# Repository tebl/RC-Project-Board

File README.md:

# RC Project Board
This year I went as far as getting myself one of those electronic games advent calendards, the kind where you get a book, a handful of components and then you get to build some a few different games using those components. Unfortunately it's one of those that only comes with a pre-programmed microcontroller and no sourcecode, so it never felt like I was building much of anything - just randomly inserting components into undocumented pins and then hope that the anonymous black box does most of the fun stuff!

Never got to the end of the book, if I'm going to build it then I'm going to build it using either an Arduino or one of my retro-computer builds - so, this project was created as a way of probably someday doing all of those things. This project is composed of two separate parts, the projet platforms boards that the retro-computer builds plugs into and the various projects that you either construct yourself on a breadboard or slot on top one of the provided PCB designs.

Pictured above is how my [RC-ONE](https://github.com/tebl/RC-ONE) looks while slotted into the [6502 Project Platform](https://github.com/tebl/RC-Project-Board/tree/master/platforms/PP%206502), the [PB-002 Covox Sound](https://github.com/tebl/RC-Project-Board/tree/master/projects/PB-002%20Covox%20Sound) project has been slotted on top instead of the usual breadboard. Below that is the [6502 Project Platform](https://github.com/tebl/RC-Project-Board/tree/master/platforms/PP%206502) with a 400 point breadboard fitting neatly on the board, if you want more space to play around you could also use the 830 point breadboard with parts of it hanging over the sides - not pretty, but oh so practical!

## Project platforms
To keep things somewhat on the simple side of things I've decided to limit myself to just doing digital I/O, leaving all of the analog stuff at the door - probably a project for another rainy day! Therefore in the context of this project I'm defining a project platform as any system capable of providing at least 16 digital I/O lines, each consists of a dedicated PCB that should take care of connecting the things together in the fashion expected by each project. Sound difficult? That just means you're probably overthinking things, the general idea is to make it so that each project would look and connects the same way no matter the platform used.

The following project platforms have been made available, refer to the table below for an overview of platforms including a separate listing each of my retro-computers that can be used with that specific platform. Note that while I hope people'll build all of my designs, you'll only need a single platform board and one of the associated systems to connect to it to get started.

| Platform | Supported system |
| -------- | --------- |
| [6502](https://github.com/tebl/RC-Project-Board/tree/master/platforms/PP%206502) | [BE6502: Build a 6502 computer](https://github.com/tebl/BE6502) |
|  | [RC-ONE: KIM-1 Replica](https://github.com/tebl/RC-ONE) |
|  | [RC6502: Apple 1 Replica](https://github.com/tebl/RC6502-Apple-1-Replica) |
|  | [RC6802 Microchicken](https://github.com/tebl/RC6802-Microchicken) |
| [Arduino](https://github.com/tebl/RC-Project-Board/tree/master/platforms/PP%20Arduino) | Arduino Nano |

## Projects
The projects are whatever you'd like to build for yourself, but if you're just looking for ideas on a few fun projects to play around with then I've probably got you covered as long as you're not looking for the most advanced stuff from someone who just dabbles in simple electronics. Most of the projects can be constructed on the breadboard by themselves by connecting the signals using female to male dupont wires (*seems most reliable that way*), but a few of the more advanced one will also come with their own PCB-designs that you can opt to build instead - these just slot on top of the platform board instead.

The breadboard oriented designs will be prefixed **BB** and a project number, similarly the ones with their own PCBs have been prefixed **PB** instead. The project number probably won't carry all that much meaning over time, so just pick something that sounds interesting and have a go at building it! Given the differences in platforms the code'll be somewhat or even completely different for each of the various systems, so there'll be varying amounts of code available for each - on the other hand, converting between them or coming up with your own versions of the code will probably be where most of the fun is at.

| Project | Description |
| ------- | ----------- |
| [PB-001 Prototyping](https://github.com/tebl/RC-Project-Board/tree/master/projects/PB-001%20Prototyping) * | Used when moving design from breadboard to a soldered together version |
| [PB-002 Covox Sound](https://github.com/tebl/RC-Project-Board/tree/master/projects/PB-002%20Covox%20Sound) * | Build a Covox sound card (sort of) |
| [PB-003 LED Cube](https://github.com/tebl/RC-Project-Board/tree/master/projects/PB-003%20LED%20Cube) * | Build one of those fancy 4x4 LED cubes |

*) Project has not been completely tested

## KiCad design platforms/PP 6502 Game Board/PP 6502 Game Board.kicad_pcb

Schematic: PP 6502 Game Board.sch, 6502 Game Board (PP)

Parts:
C1, C2, C3, C4, C5, C6, C7, C8: 100nF; C_Disc_D4.7mm_W2.5mm_P5.00mm
J1: BASE; Pin_Header_Straight_2x06_Pitch2.54mm
J2: BTM; Pin_Header_Straight_1x39_Pitch2.54mm
J3: TOP; Pin_Header_Straight_1x39_Pitch2.54mm
J4: SBC; Pin_Header_Straight_1x39_Pitch2.54mm
J5: TRS_3.5mm; Tayda_3.5mm_stereo_TRS_jack_A-853
JP1: SPKR_EN; Pin_Header_Straight_1x02_Pitch2.54mm
JP3: VIA_CLK; Pin_Header_Straight_1x03_Pitch2.54mm
LS1: Speaker; Mini_Speaker
M1, M2, M3, M4: Mounting; 1pin
Q1: 2N2222; TO-92_Molded_Narrow
R1: 100; R_Axial_DIN0207_L6.3mm_D2.5mm_P10.16mm_Horizontal
R16: 3k3; R_Axial_DIN0207_L6.3mm_D2.5mm_P10.16mm_Horizontal
R17: 470; R_Axial_DIN0207_L6.3mm_D2.5mm_P10.16mm_Horizontal
R18: 1k; R_Axial_DIN0207_L6.3mm_D2.5mm_P10.16mm_Horizontal
U1, U3: 74LS138; DIP-16_W7.62mm_Socket_LongPads
U2: 6522 VIA1; DIP-40_W15.24mm_Socket_LongPads
U4, U5, U6: 7416; DIP-14_W7.62mm_Socket
U7: 6522 VIA3; DIP-40_W15.24mm_Socket_LongPads
U8: 74LS154; DIP-24_W15.24mm_LongPads

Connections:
/4K2: J1.1, U1.14 (O1)
/4K4: J1.3, U1.13 (O2)
/4K6: J1.5, U1.12 (O3)
/4K8: J1.7, U1.11 (O4)
/4KA: J1.9, U1.10 (O5)
/4KC: J1.11, U1.9 (O6)
/A0: J4.16, U2.38, U7.38
/A1: J4.15, U2.37, U7.37
/A2: J4.14, U2.36, U7.36
/A3: J4.13, U2.35, U7.35
/A9: J4.7, U3.1 (A0)
/A10: J4.6, U3.2 (A1)
/A11: J4.5, U3.3 (A2)
/A12: J4.4, U1.5 (E2)
/A13: J4.3, U1.1 (A0)
/A14: J4.2, U1.2 (A1)
/A15: J4.1, U1.3 (A2)
/D0: J4.27, U2.33, U7.33
/D1: J4.28, U2.32, U7.32
/D2: J4.29, U2.31, U7.31
/D3: J4.30, U2.30, U7.30
/D4: J4.31, U2.29, U7.29
/D5: J4.32, U2.28, U7.28
/D6: J4.33, U2.27, U7.27
/D7: J4.34, U2.26, U7.26
/KEY_0: J3.26, U8.1 (S0)
/KEY_1: J3.25, U8.2 (S1)
/KEY_2: J3.24, U8.3 (S2)
/KEY_3: J3.23, U8.4 (S3)
/KEY_4: J3.22, U8.5 (S4)
/KEY_5: J3.21, U8.6 (S5)
/KEY_6: J3.20, U8.7 (S6)
/KEY_7: J3.19, U8.8 (S7)
/KEY_8: J3.18, U8.9 (S8)
/KEY_9: J3.17, U8.10 (S9)
/KEY_A: J3.16, U8.11 (S10)
/KEY_B: J3.11, U8.13 (S11)
/KEY_C: J3.12, U8.14 (S12)
/KEY_D: J3.13, U8.15 (S13)
/KEY_E: J3.14, U8.16 (S14)
/KEY_F: J3.15, U8.17 (S15)
/KEY_R: J3.8, R16.2, U7.9
/LED1: J3.38, U4.2
/LED2: J3.37, U4.4
/LED3: J3.36, U4.6
/LED4: J3.35, U4.8
/LED5: J3.34, U4.10
/LED6: J3.33, U4.12
/LED7: J3.32, U5.2
/LED8: J3.31, U5.4
/LED9: J3.30, U5.6
/LED10: J2.33, U5.8
/LED11: J2.34, U5.10
/LED12: J2.35, U5.12
/LED13: J2.38, U6.2
/LED14: J2.37, U6.4
/LED15: J2.36, U6.6
/PHI0: J4.21, JP3.3
/PHI2: J4.19, JP3.1
/R/~W: J4.24, U2.22, U7.22
/~IRQ: J4.22, U2.21
/~RST: J4.20, U2.34, U7.34
CLOCK: JP3.2, U2.25, U7.25
unnamed: J1.2, J1.4, J1.6, J1.8, J1.10, J1.12, U3.5 (E2)
unnamed: J5.2, J5.5, R1.2
unnamed: JP1.1, Q1.2, R18.2
unnamed: JP1.2, R1.1, U7.17
unnamed: LS1.1, Q1.3, R17.1
unnamed: U2.2, U4.1
unnamed: U2.3, U4.3
unnamed: U2.4, U4.5
unnamed: U2.5, U4.9
unnamed: U2.6, U4.11
unnamed: U2.7, U4.13
unnamed: U2.8, U5.1
unnamed: U2.9, U5.3
unnamed: U2.10, U5.5
unnamed: U2.11, U5.9
unnamed: U2.12, U5.11
unnamed: U2.13, U5.13
unnamed: U2.14, U6.1
unnamed: U2.15, U6.3
unnamed: U2.17, U6.5
unnamed: U7.10, U8.23 (A0)
unnamed: U7.11, U8.22 (A1)
unnamed: U7.12, U8.21 (A2)
unnamed: U7.13, U8.20 (A3)
VCC: C1.1, C2.1, C3.1, C4.1, C5.1, C6.1, C7.1, C8.1, J2.1, J2.39, J3.1, J3.39, J4.18, R16.1, R17.2, R18.1, U1.6 (E3), U1.16 (VCC), U2.20, U2.24, U3.6 (E3), U3.16 (VCC), U4.14, U5.14, U6.14, U7.20, U7.24, U8.24 (VCC)
~VIA1: U2.23, U3.15 (O0)
~VIA3: U3.9 (O6), U7.23

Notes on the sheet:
$2000
$4000
$6000
$8000
$A000
$C000
$x000
$xE00
$x400
$x200
$x600
$x800
$xC00
$xA00
Rodney Zaks wrote a whole book of games for the SYM-1 and I wanted to build it for use with my computers as well. so this board takes care of the logic needed for a 6502 or 6800 based computer. Also requires the game board project fitted on top as it contains all of the interactive parts needed.

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
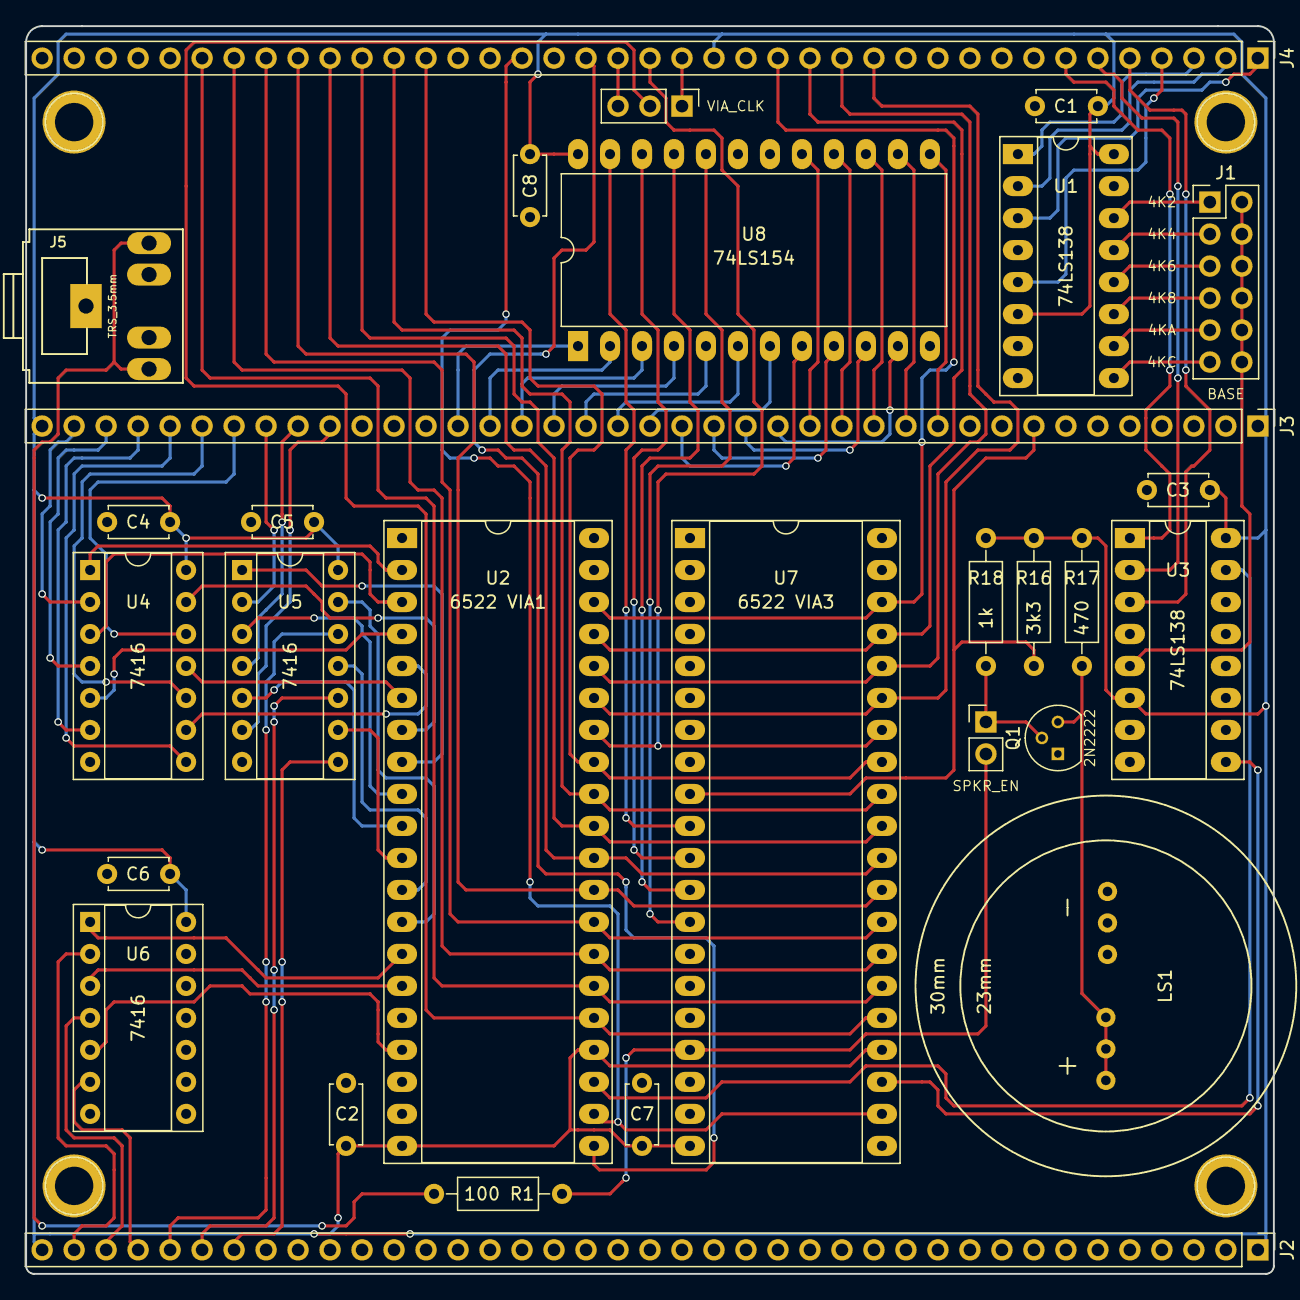
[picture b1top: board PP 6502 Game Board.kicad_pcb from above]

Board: 2 copper layers, 99.1 x 99.1 mm, 33 parts (0 on the bottom side), 91 nets.

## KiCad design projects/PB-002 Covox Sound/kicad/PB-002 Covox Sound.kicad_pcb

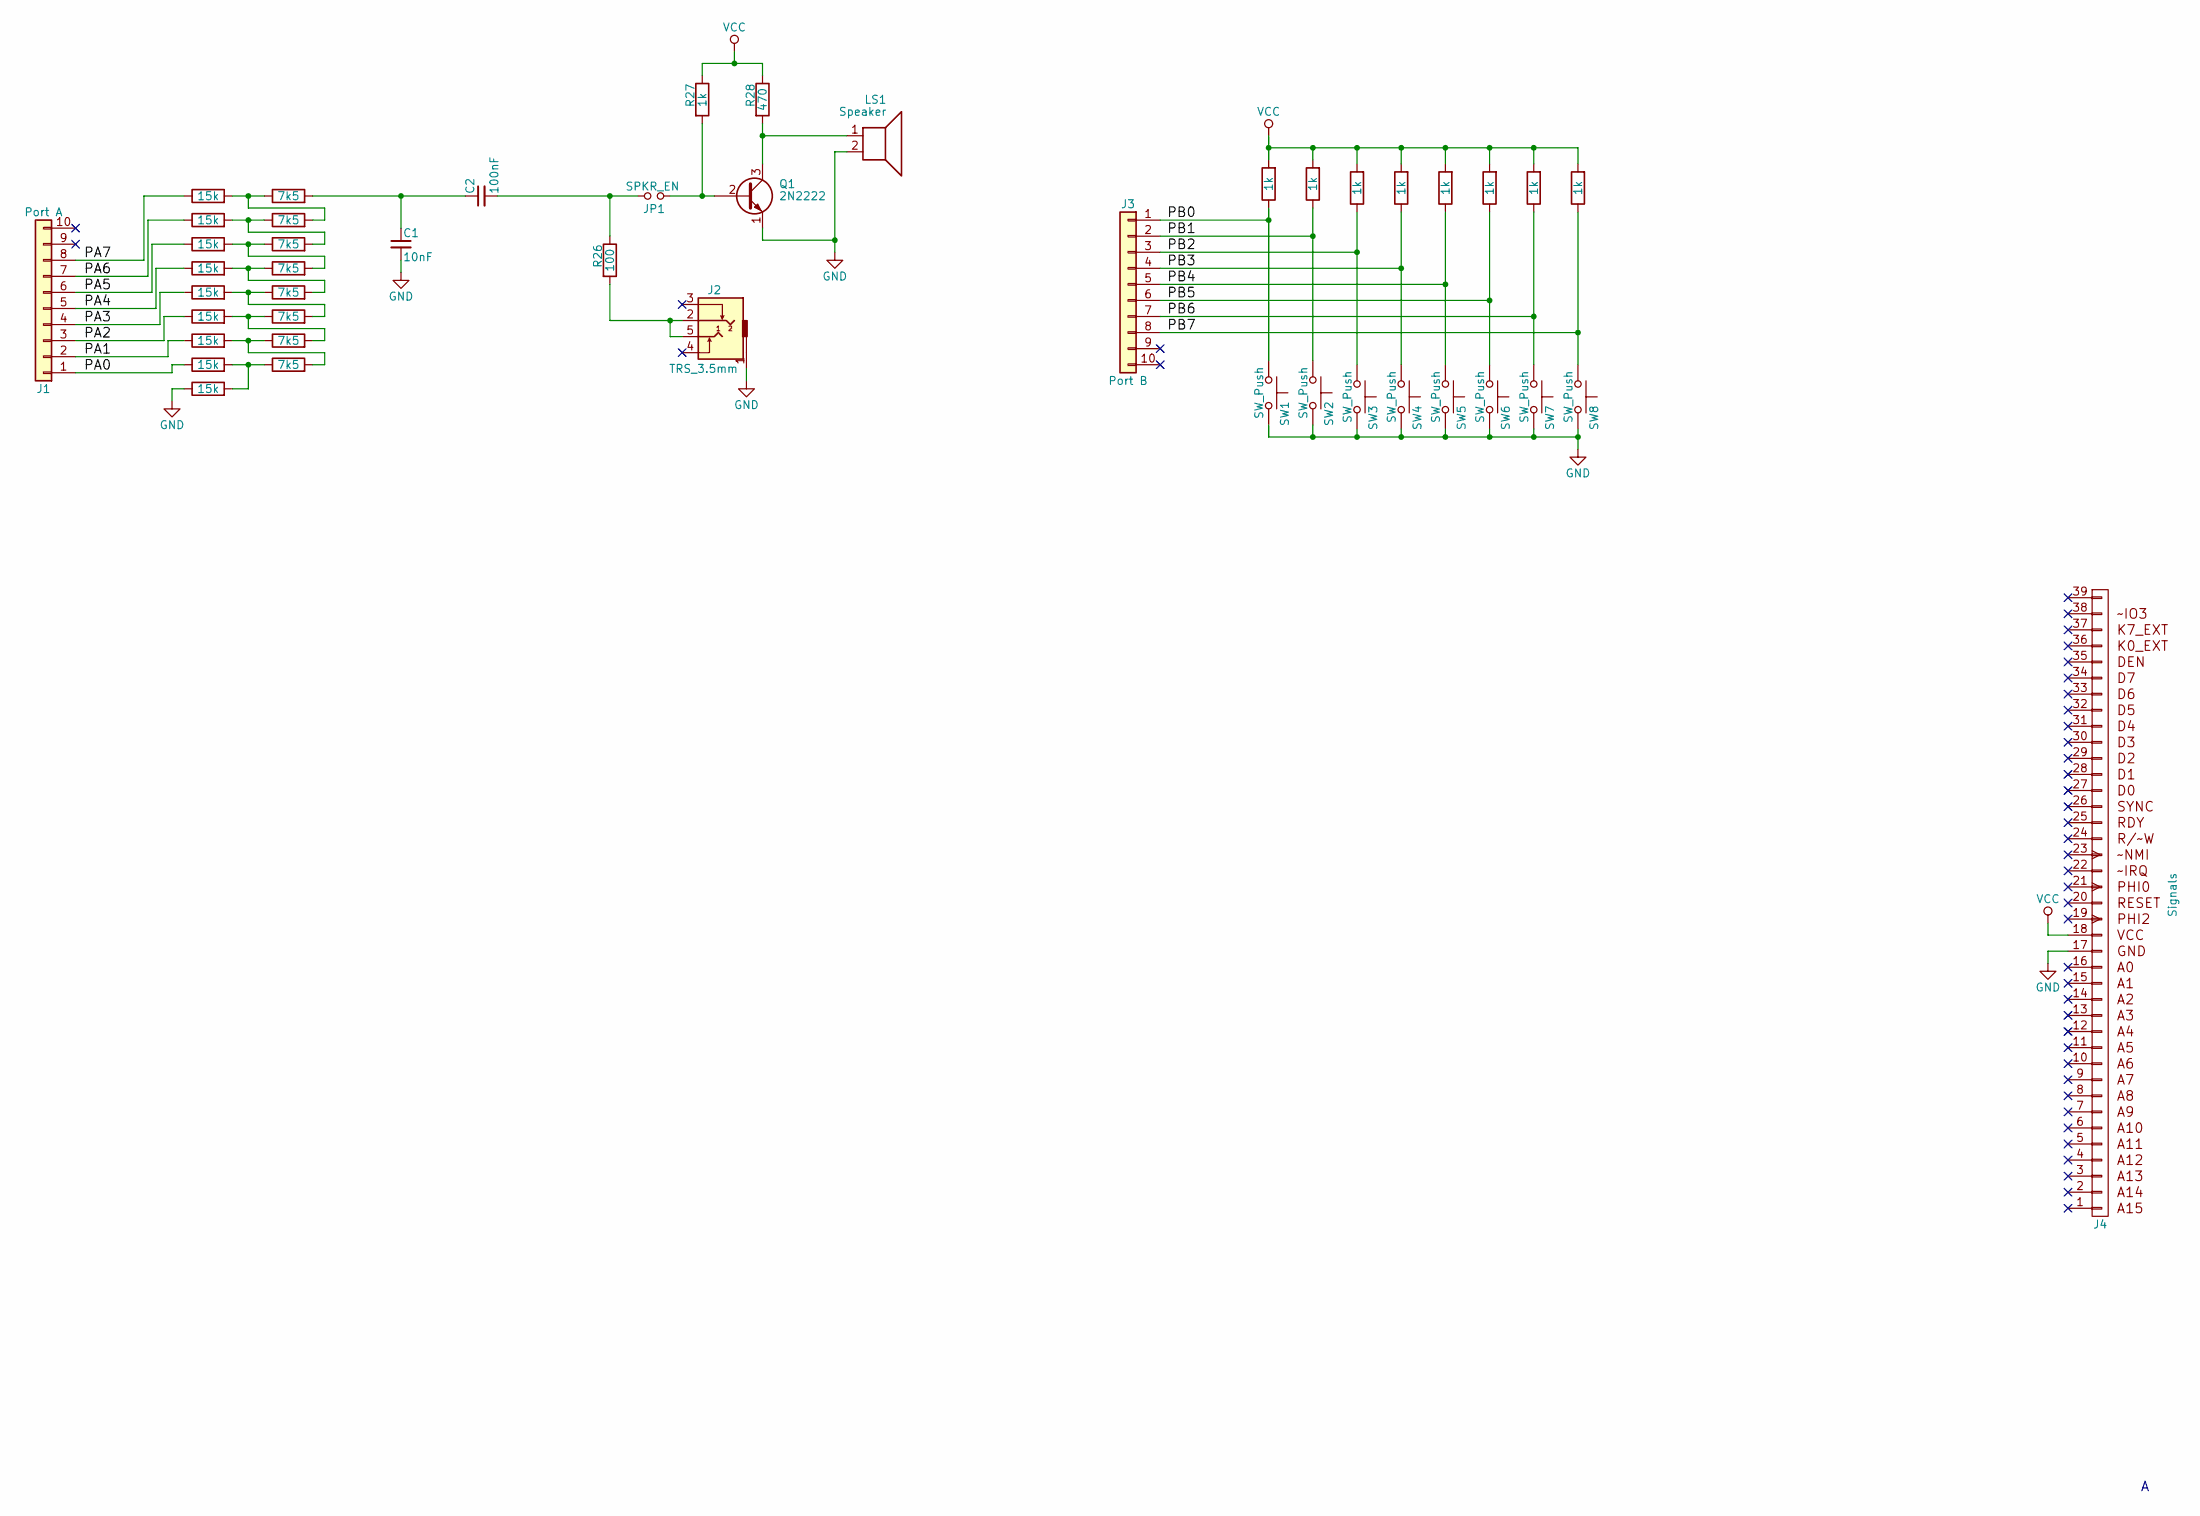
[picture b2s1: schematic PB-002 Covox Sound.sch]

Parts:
C1: 10nF; C_Disc_D4.7mm_W2.5mm_P5.00mm
C2: 100nF; C_Disc_D4.7mm_W2.5mm_P5.00mm
J1: Port A; Pin_Header_Straight_1x10_Pitch2.54mm
J2: TRS_3.5mm; Tayda_3.5mm_stereo_TRS_jack_A-853
J3: Port B; Pin_Header_Straight_1x10_Pitch2.54mm
J4: Signals; Pin_Header_Straight_1x39_Pitch2.54mm
JP1: SPKR_EN; Pin_Header_Straight_1x02_Pitch2.54mm
LS1: Speaker; Mini_Speaker
Q1: 2N2222; TO-92_Molded_Narrow
R1, R2, R3, R4, R5, R6, R7, R8, R9: 15k; R_Axial_DIN0207_L6.3mm_D2.5mm_P10.16mm_Horizontal
R10, R11, R12, R13, R14, R15, R16, R17: 7k5; R_Axial_DIN0207_L6.3mm_D2.5mm_P10.16mm_Horizontal
R18, R19, R20, R21, R22, R23, R24, R25, R27: 1k; R_Axial_DIN0207_L6.3mm_D2.5mm_P10.16mm_Horizontal
R26: 100; R_Axial_DIN0207_L6.3mm_D2.5mm_P10.16mm_Horizontal
R28: 470; R_Axial_DIN0207_L6.3mm_D2.5mm_P10.16mm_Horizontal
SW1, SW2, SW3, SW4, SW5, SW6, SW7, SW8: SW_Push; SW_PUSH_6mm

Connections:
/PA0: J1.1, R8.1
/PA1: J1.2, R7.1
/PA2: J1.3, R6.1
/PA3: J1.4, R5.1
/PA4: J1.5, R4.1
/PA5: J1.6, R3.1
/PA6: J1.7, R2.1
/PA7: J1.8, R1.1
/PB0: J3.1, R18.1, SW1.1
/PB1: J3.2, R19.1, SW2.1
/PB2: J3.3, R20.1, SW3.1
/PB3: J3.4, R21.1, SW4.1
/PB4: J3.5, R22.1, SW5.1
/PB5: J3.6, R23.1, SW6.1
/PB6: J3.7, R24.1, SW7.1
/PB7: J3.8, R25.1, SW8.1
GND: C1.2, J2.1, J4.17, LS1.2, Q1.1 (E), R9.1, SW1.2, SW2.2, SW3.2, SW4.2, SW5.2, SW6.2, SW7.2, SW8.2
unnamed: C1.1, C2.1, R10.2
unnamed: C2.2, JP1.2, R26.1
unnamed: J2.2, J2.5, R26.2
unnamed: JP1.1, Q1.2 (B), R27.2
unnamed: LS1.1, Q1.3 (C), R28.2
unnamed: R1.2, R10.1, R11.2
unnamed: R2.2, R11.1, R12.2
unnamed: R3.2, R12.1, R13.2
unnamed: R4.2, R13.1, R14.2
unnamed: R5.2, R14.1, R15.2
unnamed: R6.2, R15.1, R16.2
unnamed: R7.2, R16.1, R17.2
unnamed: R8.2, R9.2, R17.1
VCC: J4.18, R18.2, R19.2, R20.2, R21.2, R22.2, R23.2, R24.2, R25.2, R27.1, R28.1

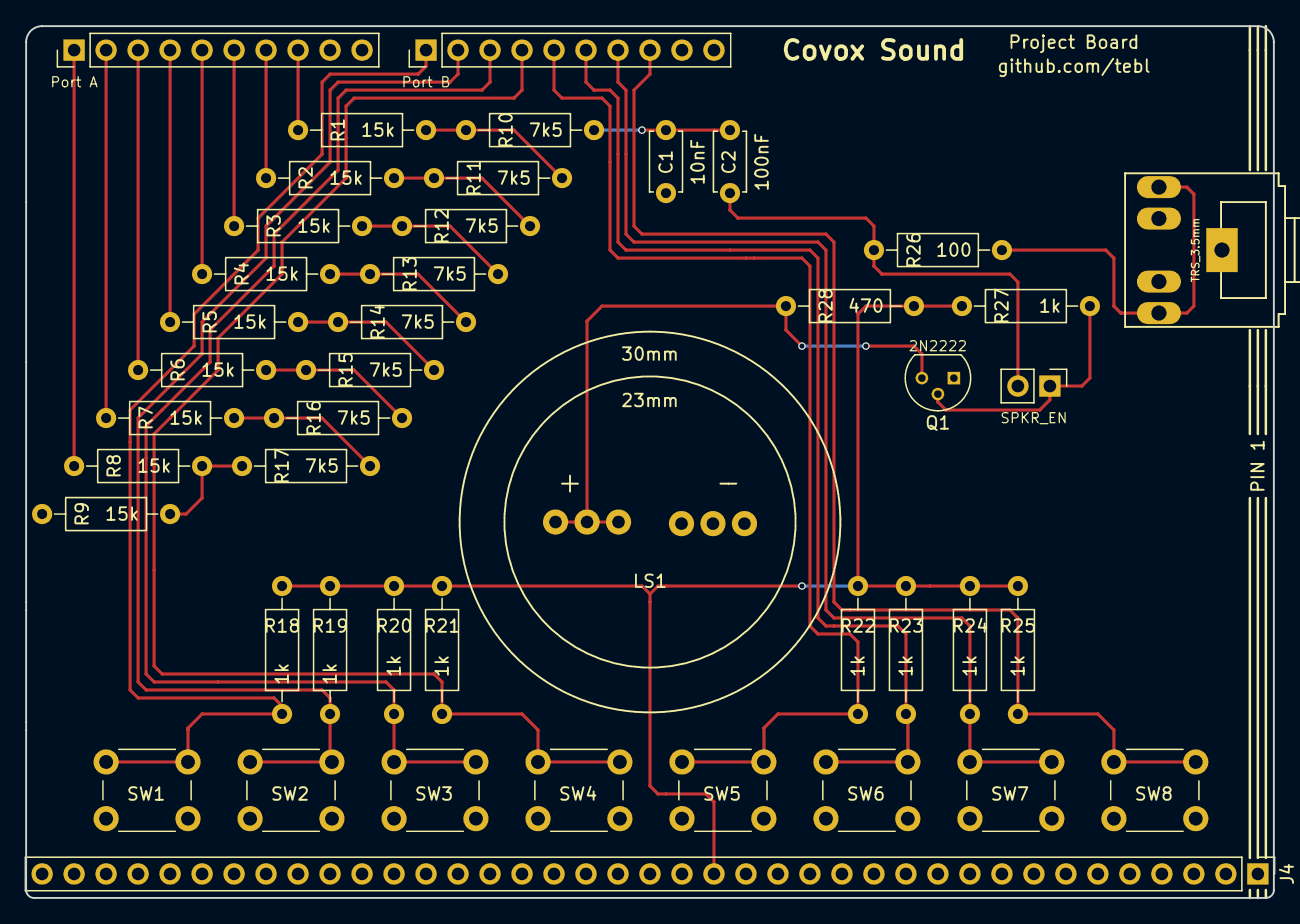
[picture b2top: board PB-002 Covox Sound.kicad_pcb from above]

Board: 2 copper layers, 99.1 x 69.2 mm, 45 parts (0 on the bottom side), 31 nets.

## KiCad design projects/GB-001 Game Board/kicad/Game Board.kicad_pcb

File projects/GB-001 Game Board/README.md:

# GB-001 Game Board
I recently picked up a copy of *6502 Games* by the author of a lot of great books about the 6502-processor, the one and only Rodnay Zaks. Wanted to write the late, great Rodnay Zaks though as far as Wikipedia has been updated he's still alive so I'll have to settle with *"great"*.  Love his books, so it was an obvious purchase though I had to have it sent half-way across the world to get it - Canada to Norway, so it basically went from one icy tundra to another one! You however don't need the physical book to enjoy it, I'm just old-fashioned that way, as there's a digitized copy available on [archive.org](https://archive.org/details/6502GamesRodnayZaks/mode/2up).

I was unsure of whether or not to include the game board as it contradicts the overall goal of this repository (Project Board), but decided for it as the project is definitely in the spirit of the project (and it's my project, so I get to decide). Despite not fitting on a standard platform board, I opted for going with the notion that it uses a lot of the same components and shares the general nature of being usable on all of my 6502-based computers.

## Requirements
Project platforms supported:
* [PP 6502 Game Board](https://github.com/tebl/RC-Project-Board/tree/master/platforms/PP%206502%20Game%20Board)

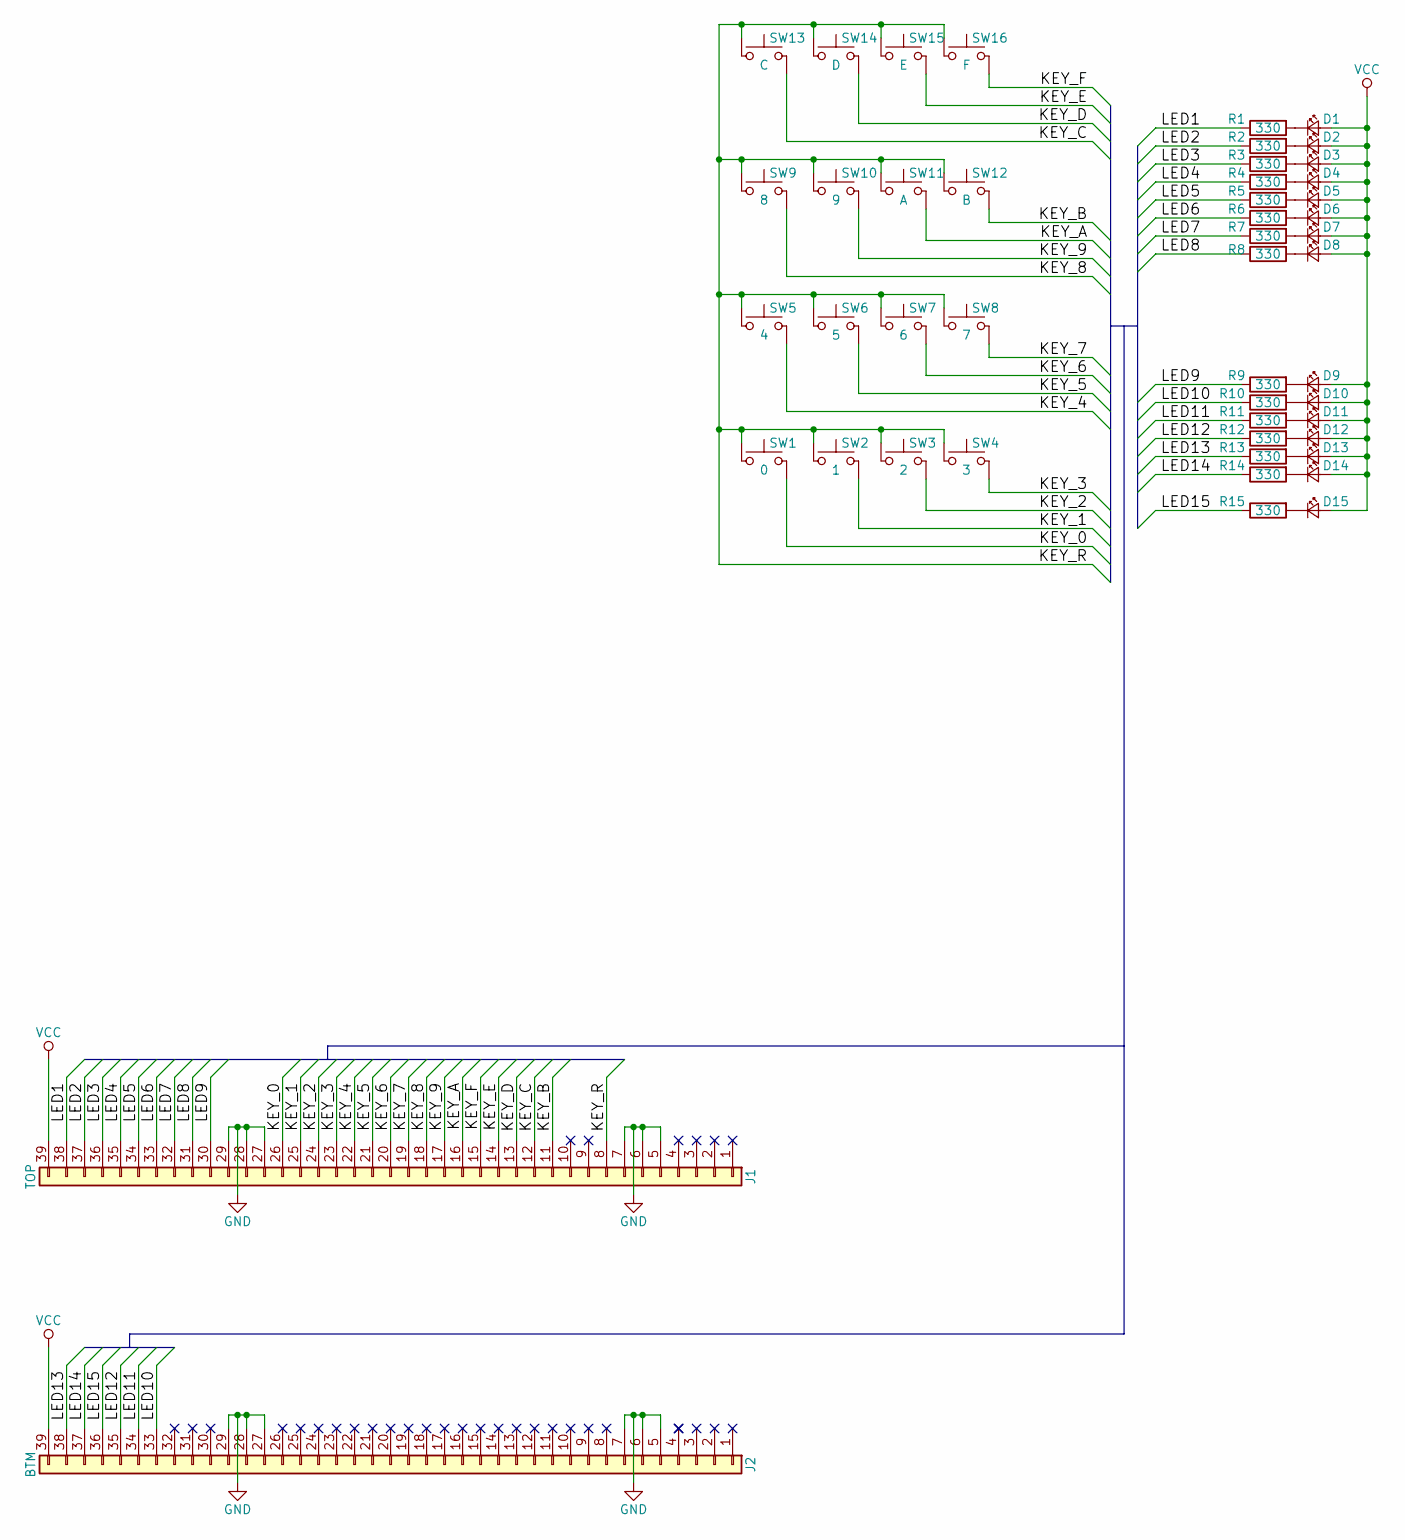
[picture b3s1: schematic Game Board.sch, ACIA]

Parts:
D1, D2, D3, D4, D5, D6, D7, D8, D9, D10, D11, D12, D13, D14, D15: LED; LED_D5.0mm
J1: TOP; Pin_Header_Straight_1x39_Pitch2.54mm
J2: BTM; Pin_Header_Straight_1x39_Pitch2.54mm
R1, R2, R3, R4, R5, R6, R7, R8, R9, R10, R11, R12, R13, R14, R15: 330; R_Axial_DIN0207_L6.3mm_D2.5mm_P10.16mm_Horizontal
SW1: 0; SW_PUSH_6mm
SW2: 1; SW_PUSH_6mm
SW3: 2; SW_PUSH_6mm
SW4: 3; SW_PUSH_6mm
SW5: 4; SW_PUSH_6mm
SW6: 5; SW_PUSH_6mm
SW7: 6; SW_PUSH_6mm
SW8: 7; SW_PUSH_6mm
SW9: 8; SW_PUSH_6mm
SW10: 9; SW_PUSH_6mm
SW11: A; SW_PUSH_6mm
SW12: B; SW_PUSH_6mm
SW13: C; SW_PUSH_6mm
SW14: D; SW_PUSH_6mm
SW15: E; SW_PUSH_6mm
SW16: F; SW_PUSH_6mm

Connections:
/KEY_0: J1.26, SW1.2
/KEY_1: J1.25, SW2.2
/KEY_2: J1.24, SW3.2
/KEY_3: J1.23, SW4.2
/KEY_4: J1.22, SW5.2
/KEY_5: J1.21, SW6.2
/KEY_6: J1.20, SW7.2
/KEY_7: J1.19, SW8.2
/KEY_8: J1.18, SW9.2
/KEY_9: J1.17, SW10.2
/KEY_A: J1.16, SW11.2
/KEY_B: J1.11, SW12.2
/KEY_C: J1.12, SW13.2
/KEY_D: J1.13, SW14.2
/KEY_E: J1.14, SW15.2
/KEY_F: J1.15, SW16.2
/KEY_R: J1.8, SW1.1, SW2.1, SW3.1, SW4.1, SW5.1, SW6.1, SW7.1, SW8.1, SW9.1, SW10.1, SW11.1, SW12.1, SW13.1, SW14.1, SW15.1, SW16.1
/LED1: J1.38, R1.1
/LED2: J1.37, R2.1
/LED3: J1.36, R3.1
/LED4: J1.35, R4.1
/LED5: J1.34, R5.1
/LED6: J1.33, R6.1
/LED7: J1.32, R7.1
/LED8: J1.31, R8.1
/LED9: J1.30, R9.1
/LED10: J2.33, R10.1
/LED11: J2.34, R11.1
/LED12: J2.35, R12.1
/LED13: J2.38, R13.1
/LED14: J2.37, R14.1
/LED15: J2.36, R15.1
GND: J1.5, J1.6, J1.7, J1.27, J1.28, J1.29, J2.5, J2.6, J2.7, J2.27, J2.28, J2.29
unnamed: D1.1 (K), R1.2
unnamed: D2.1 (K), R2.2
unnamed: D3.1 (K), R3.2
unnamed: D4.1 (K), R4.2
unnamed: D5.1 (K), R5.2
unnamed: D6.1 (K), R6.2
unnamed: D7.1 (K), R7.2
unnamed: D8.1 (K), R8.2
unnamed: D9.1 (K), R9.2
unnamed: D10.1 (K), R10.2
unnamed: D11.1 (K), R11.2
unnamed: D12.1 (K), R12.2
unnamed: D13.1 (K), R13.2
unnamed: D14.1 (K), R14.2
unnamed: D15.1 (K), R15.2
VCC: D1.2 (A), D2.2 (A), D3.2 (A), D4.2 (A), D5.2 (A), D6.2 (A), D7.2 (A), D8.2 (A), D9.2 (A), D10.2 (A), D11.2 (A), D12.2 (A), D13.2 (A), D14.2 (A), D15.2 (A), J1.39, J2.39

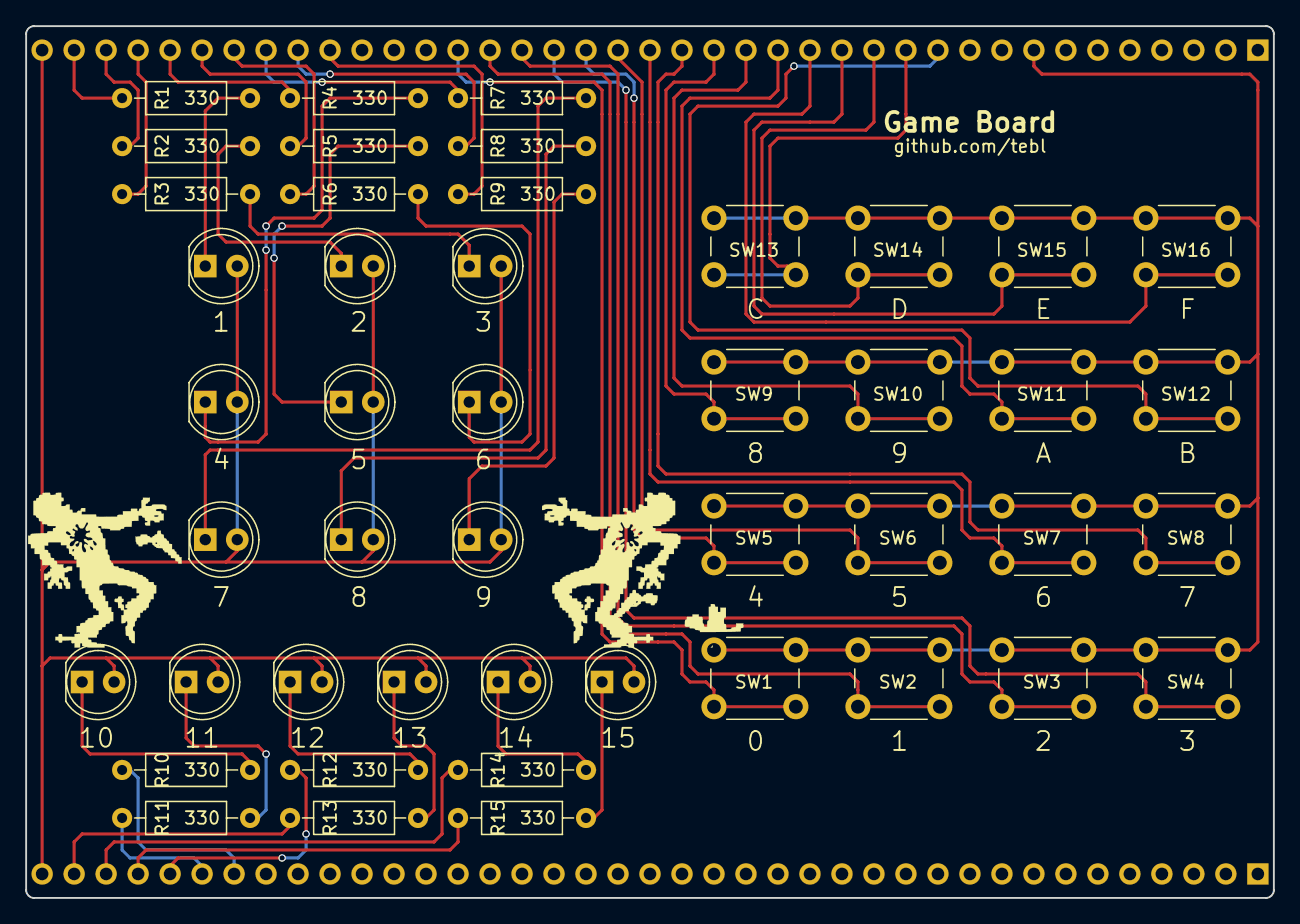
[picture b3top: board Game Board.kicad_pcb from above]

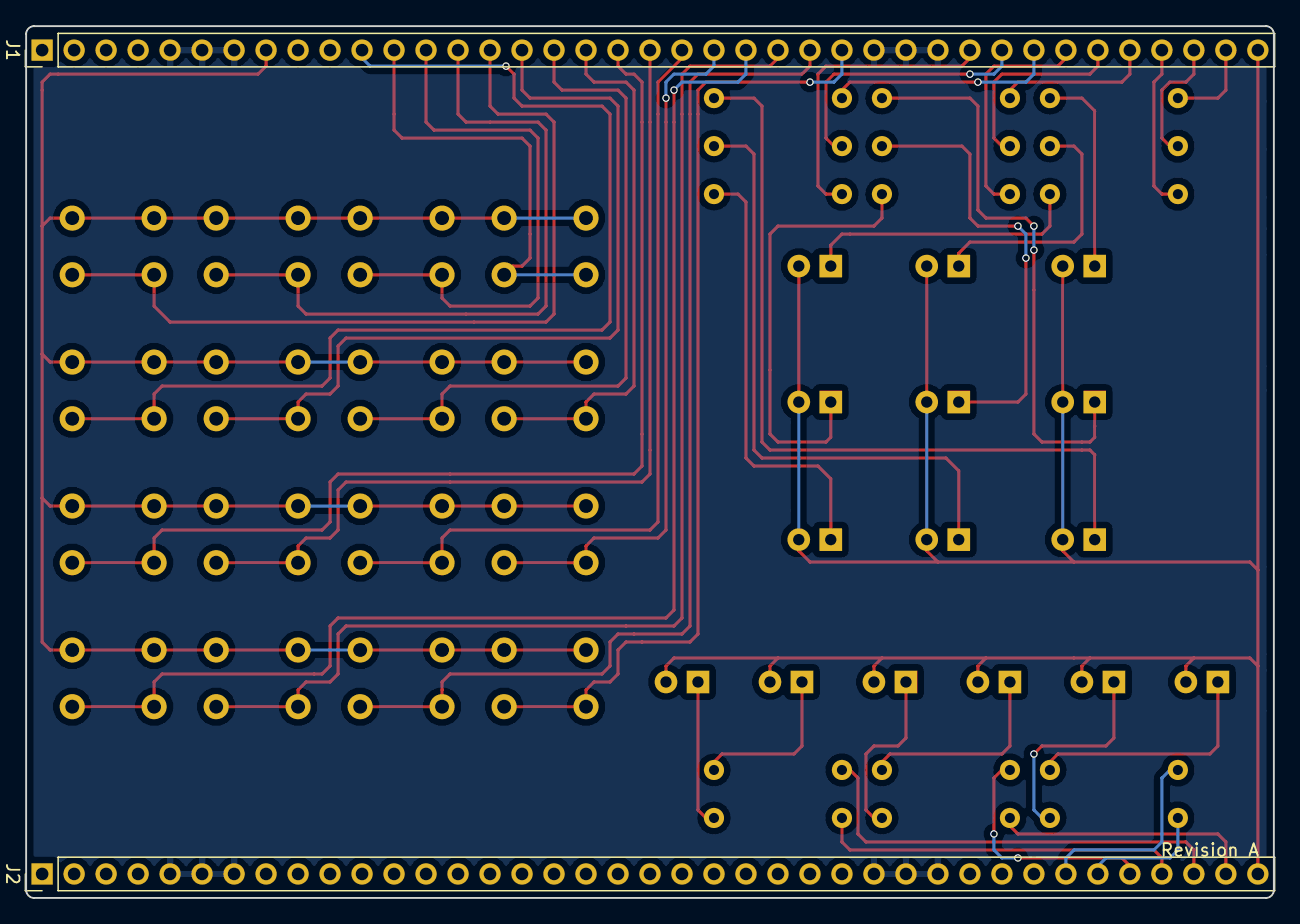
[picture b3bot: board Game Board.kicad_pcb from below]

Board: 2 copper layers, 99.1 x 69.2 mm, 48 parts (2 on the bottom side), 49 nets.

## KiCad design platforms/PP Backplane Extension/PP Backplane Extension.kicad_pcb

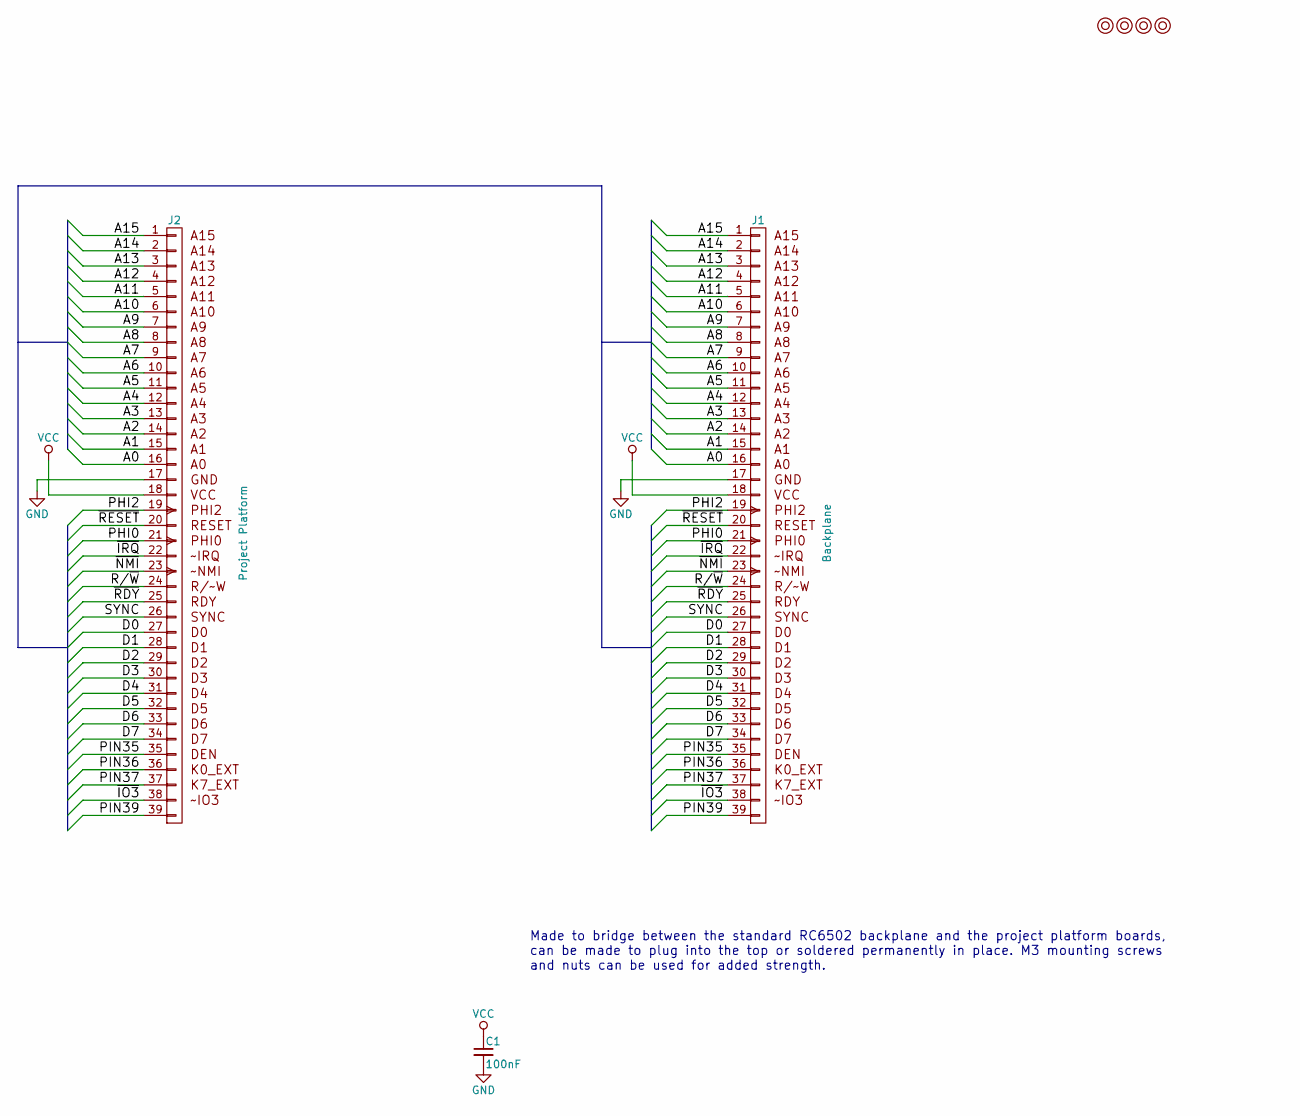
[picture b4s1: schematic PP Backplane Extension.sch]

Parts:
C1: 100nF; C_Disc_D4.7mm_W2.5mm_P5.00mm
J1: Backplane; Pin_Header_Straight_1x39_Pitch2.54mm
J2: Project Platform; Pin_Header_Straight_1x39_Pitch2.54mm
M1, M2, M3, M4: Mounting; 1pin

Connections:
/A0: J1.16 (A0), J2.16 (A0)
/A1: J1.15 (A1), J2.15 (A1)
/A2: J1.14 (A2), J2.14 (A2)
/A3: J1.13 (A3), J2.13 (A3)
/A4: J1.12 (A4), J2.12 (A4)
/A5: J1.11 (A5), J2.11 (A5)
/A6: J1.10 (A6), J2.10 (A6)
/A7: J1.9 (A7), J2.9 (A7)
/A8: J1.8 (A8), J2.8 (A8)
/A9: J1.7 (A9), J2.7 (A9)
/A10: J1.6 (A10), J2.6 (A10)
/A11: J1.5 (A11), J2.5 (A11)
/A12: J1.4 (A12), J2.4 (A12)
/A13: J1.3 (A13), J2.3 (A13)
/A14: J1.2 (A14), J2.2 (A14)
/A15: J1.1 (A15), J2.1 (A15)
/D0: J1.27 (D0), J2.27 (D0)
/D1: J1.28 (D1), J2.28 (D1)
/D2: J1.29 (D2), J2.29 (D2)
/D3: J1.30 (D3), J2.30 (D3)
/D4: J1.31 (D4), J2.31 (D4)
/D5: J1.32 (D5), J2.32 (D5)
/D6: J1.33 (D6), J2.33 (D6)
/D7: J1.34 (D7), J2.34 (D7)
/PHI0: J1.21 (PHI0), J2.21 (PHI0)
/PHI2: J1.19 (PHI2), J2.19 (PHI2)
/PIN35: J1.35 (TX), J2.35 (TX)
/PIN36: J1.36 (RX), J2.36 (RX)
/PIN37: J1.37 (NMI), J2.37 (NMI)
/PIN39: J1.39, J2.39
/R/~W: J1.24 (RW), J2.24 (RW)
/SYNC: J1.26 (SYNC), J2.26 (SYNC)
/~IO3: J1.38, J2.38
/~IRQ: J1.22 (IRQ), J2.22 (IRQ)
/~NMI: J1.23 (PHI1), J2.23 (PHI1)
/~RDY: J1.25 (READY), J2.25 (READY)
/~RESET: J1.20 (RESET), J2.20 (RESET)
GND: C1.2, J1.17, J2.17
VCC: C1.1, J1.18, J2.18

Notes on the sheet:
Made to bridge between the standard RC6502 backplane and the project platform boards, can be made to plug into the top or soldered permanently in place. M3 mounting screws and nuts can be used for added strength.

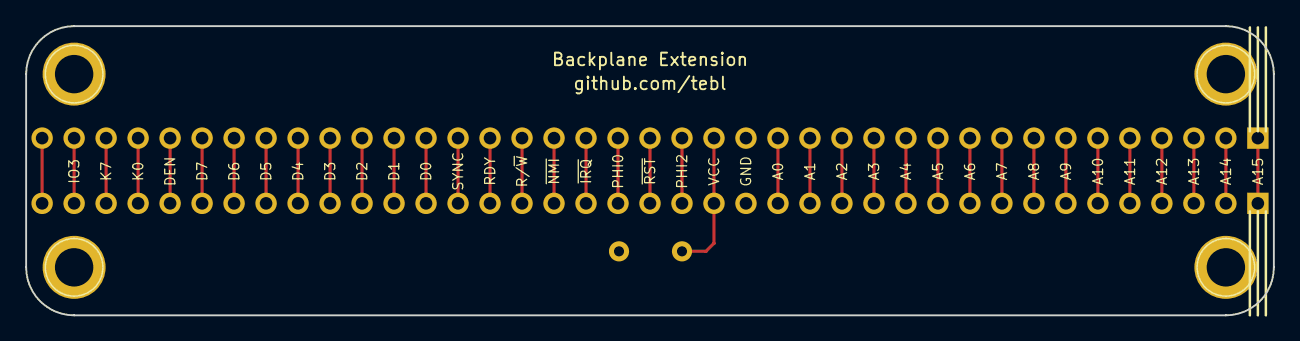
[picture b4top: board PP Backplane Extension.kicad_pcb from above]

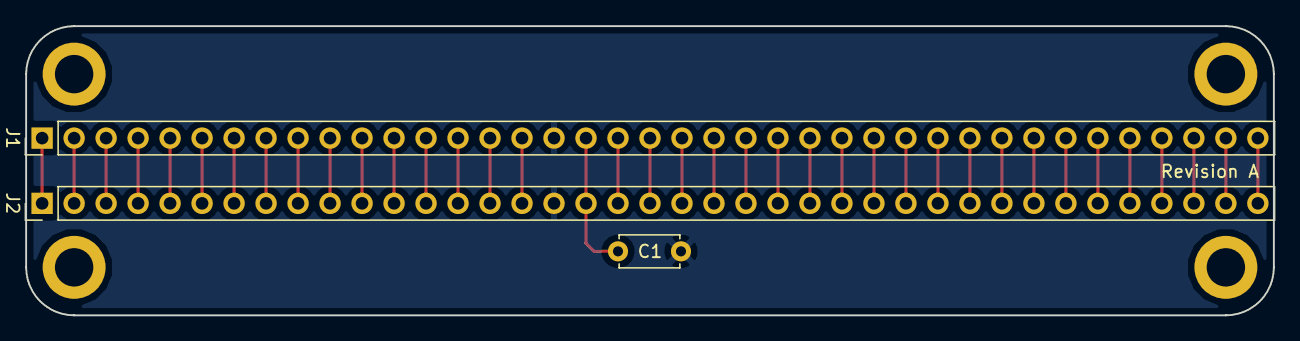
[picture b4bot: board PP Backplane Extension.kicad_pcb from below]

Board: 2 copper layers, 99.1 x 23.0 mm, 7 parts (3 on the bottom side), 39 nets.
